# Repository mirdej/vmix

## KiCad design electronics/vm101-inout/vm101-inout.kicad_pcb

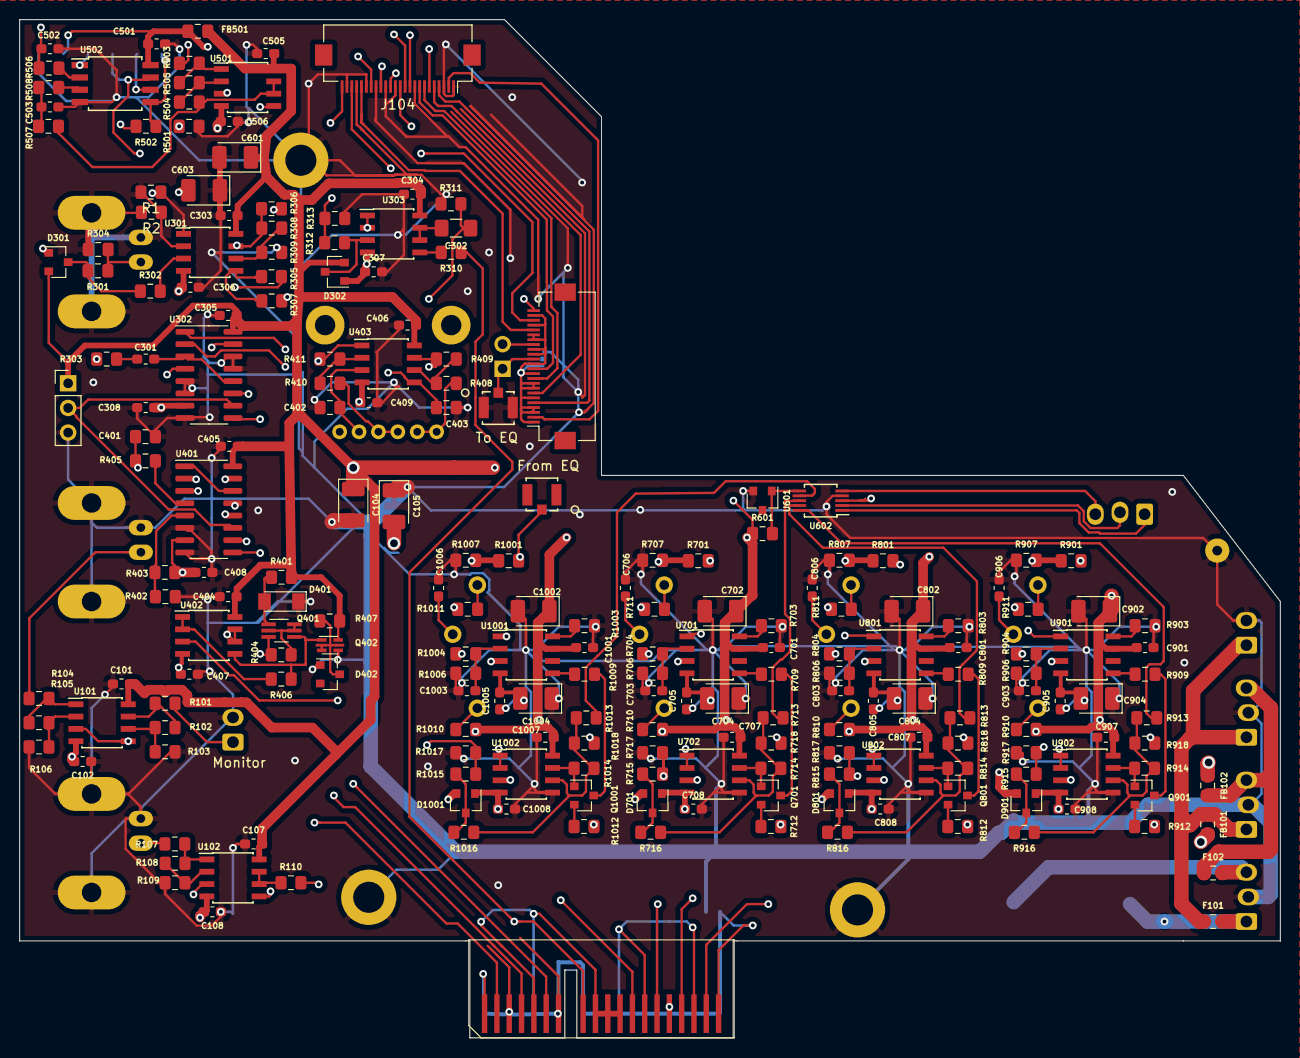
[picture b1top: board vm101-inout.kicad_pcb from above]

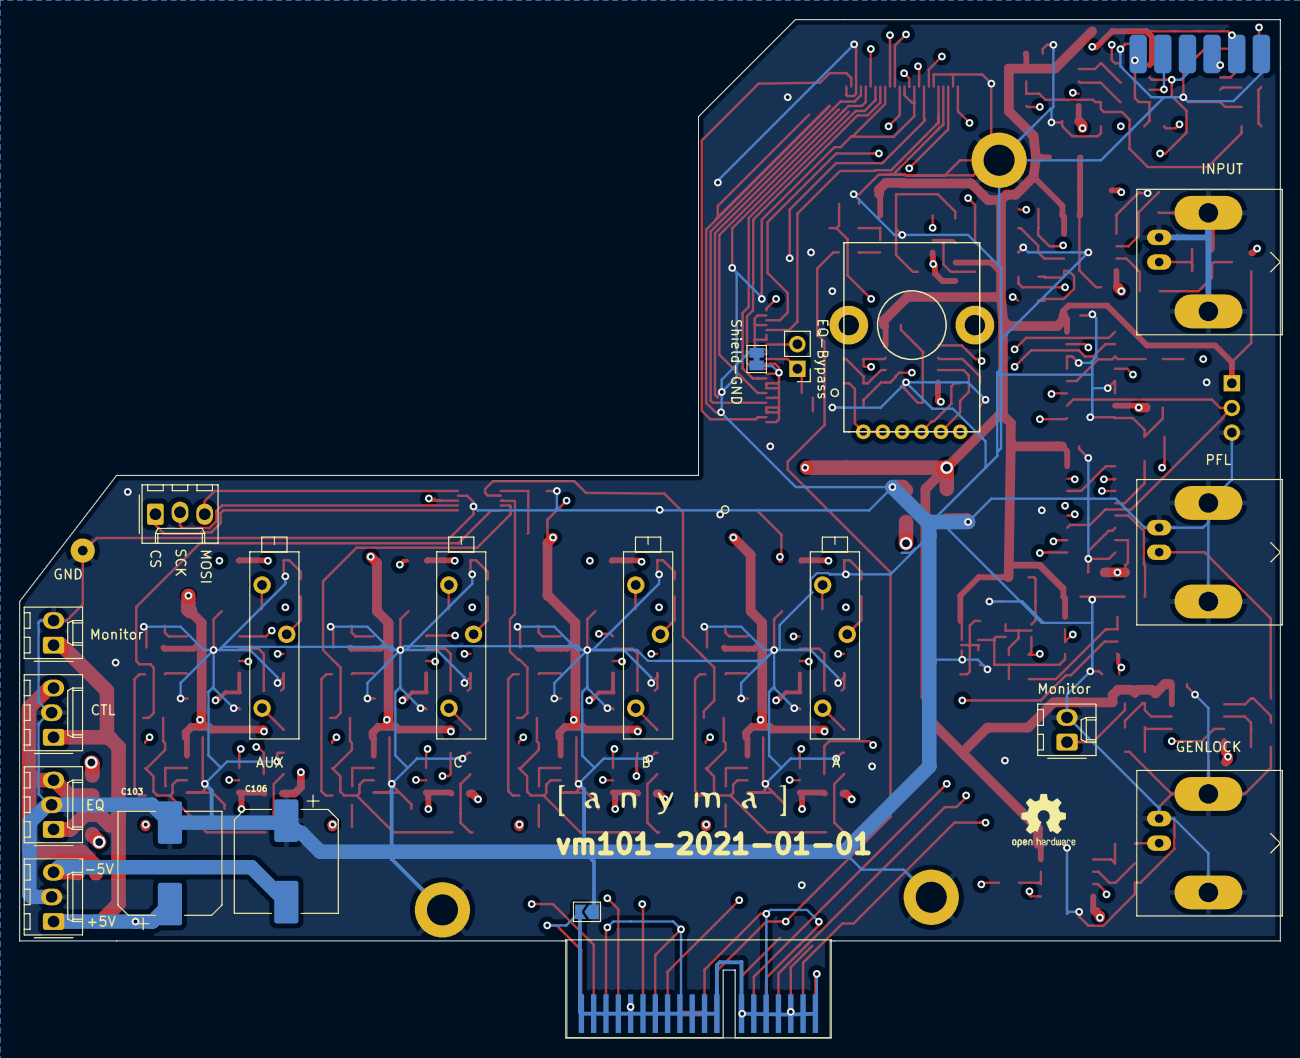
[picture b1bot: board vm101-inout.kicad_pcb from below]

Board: 4 copper layers, 130.0 x 105.0 mm, 238 parts (22 on the bottom side), 150 nets.

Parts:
C101, C102, C107, C108, C303, C304, C305, C306, C307, C308, C404, C405, C406, C407, C408, C409, C501, C505, C506, C701, C705, C707, C708, C801, C805, C807, C808, C901, C905, C907, C908, C1001, C1005, C1007, C1008: 100n; C_0603_1608Metric_Pad1.05x0.95mm_HandSolder
C103, C106: 220u; CP_Elec_10x10.5
C104, C105, C601, C603: 10u; CP_EIA-3528-21_Kemet-B_Pad1.50x2.35mm_HandSolder
C301, C703, C706, C803, C806, C903, C906, C1003, C1006: 1u; C_0603_1608Metric_Pad1.05x0.95mm_HandSolder
C302: 0-Ohm; C_1206_3216Metric_Pad1.42x1.75mm_HandSolder
C401: don't; C_0805_2012Metric_Pad1.15x1.40mm_HandSolder
C402, C403: 10p; C_0805_2012Metric_Pad1.15x1.40mm_HandSolder
C502, C503: C_Small; C_0603_1608Metric_Pad1.05x0.95mm_HandSolder
C702, C704, C802, C804, C902, C904, C1002, C1004: 4u7; CP_EIA-3528-21_Kemet-B_Pad1.50x2.35mm_HandSolder
D301, D302, D701, D801, D901, D1001: BAT54S; SOT-23
D401: D; D_MiniMELF
D402: BAT54; D_SOT-23_ANK
F101, F102: Polyfuse; Fuse_0805_2012Metric
FB101, FB102: 330u; L_0805_2012Metric_Pad1.15x1.40mm_HandSolder
FB501: Ferrit(flash levelmeter first); L_0805_2012Metric_Pad1.15x1.40mm_HandSolder
H601, H602, H603: MountingHole_Pad; MountingHole_3.2mm_M3_ISO7380_Pad
J101: Conn_Coaxial; BNC_Amphenol_B6252HB-NPP3G-50_Horizontal
J102: MONITOR_OUT; Molex_KK-254_AE-6410-02A_1x02_P2.54mm_Vertical
J103: To EQ; Hirose_FH12-24S-0.5SH_1x24-1MP_P0.50mm_Horizontal
J104: Conn_01x24_Shielded; Hirose_FH12-24S-0.5SH_1x24-1MP_P0.50mm_Horizontal
J105: PFL-OUT; BNC_Amphenol_B6252HB-NPP3G-50_Horizontal
J106: GENLOCK-OUT; BNC_Amphenol_B6252HB-NPP3G-50_Horizontal
J107: gnd; Solderpad_1mm
J108: Monitor-Power; Molex_KK-254_AE-6410-02A_1x02_P2.54mm_Vertical
J109: EQ-Power; Molex_KK-254_AE-6410-03A_1x03_P2.54mm_Vertical
J110: Controller-Power; Molex_KK-254_AE-6410-03A_1x03_P2.54mm_Vertical
J111: Card-Edge_02x20_Odd_Even; Samtec_MECF-20-0_-L-DV_2x20_P1.27mm_Polarized_Edge
J112: Power; Molex_KK-254_AE-6410-03A_1x03_P2.54mm_Vertical
J113: Conn_01x03; PinHeader_1x03_P2.54mm_Vertical
J114, J115: TE_UMCC_2337019-1
J601: Conn_01x03; Molex_KK-254_AE-6410-03A_1x03_P2.54mm_Vertical
JP101: Jumper_2_Open; PinHeader_1x02_P2.54mm_Vertical
JP102: Jumper; SolderJumper-2_P1.3mm_Bridged_Pad1.0x1.5mm
JP103: Jumper; SolderJumper-2_P1.3mm_Open_TrianglePad1.0x1.5mm
Q401: PMBT3906YS; SOT-363_SC-70-6_Handsoldering
Q402: PEMX1; SOT-666
Q701, Q801, Q901, Q1001: PNP; SOT-23_BEC
R1: 680; R_0805_2012Metric_Pad1.15x1.40mm_HandSolder
R2: 1k6; R_0805_2012Metric_Pad1.15x1.40mm_HandSolder
R101, R104, R107, R110, R301, R302, R303, R304, R306, R310, R312, R506, R508: 75; R_0805_2012Metric_Pad1.15x1.40mm_HandSolder
R102, R103, R105, R106, R108, R109, R408, R409, R410, R411: 220; R_0805_2012Metric_Pad1.15x1.40mm_HandSolder
R305, R307, R308, R309, R501, R503, R504, R505, R507: 3k3; R_0805_2012Metric_Pad1.15x1.40mm_HandSolder
R311: don't; R_0805_2012Metric_Pad1.15x1.40mm_HandSolder
R313: 10k; R_0805_2012Metric_Pad1.15x1.40mm_HandSolder
R401, R405, R703, R803, R903, R1003: 120; R_0805_2012Metric_Pad1.15x1.40mm_HandSolder
R402, R406, R502: 300; R_0805_2012Metric_Pad1.15x1.40mm_HandSolder
R403: 4k7; R_0805_2012Metric_Pad1.15x1.40mm_HandSolder
R404: 5k6; R_0805_2012Metric_Pad1.15x1.40mm_HandSolder
R407, R717, R817, R917, R1017: 47k; R_0805_2012Metric_Pad1.15x1.40mm_HandSolder
R601: 560; R_0805_2012Metric_Pad1.15x1.40mm_HandSolder
R701, R709, R801, R809, R901, R909, R1001, R1009: 1k; R_0805_2012Metric_Pad1.15x1.40mm_HandSolder
R704, R710, R711, R804, R810, R811, R904, R910, R911, R1004, R1010, R1011: 3k; R_0805_2012Metric_Pad1.15x1.40mm_HandSolder
R706, R707, R715, R806, R807, R815, R906, R907, R915, R1006, R1007, R1015: 100; R_0805_2012Metric_Pad1.15x1.40mm_HandSolder
R712, R812, R912, R1012: 2k2; R_0805_2012Metric_Pad1.15x1.40mm_HandSolder
R713, R716, R813, R816, R913, R916, R1013, R1016: 12K; R_0805_2012Metric_Pad1.15x1.40mm_HandSolder
R714, R814, R914, R1014: 20k; R_0805_2012Metric_Pad1.15x1.40mm_HandSolder
R718, R818, R918, R1018: 22k; R_0805_2012Metric_Pad1.15x1.40mm_HandSolder
RV401: R_POT_Dual; RK12L123
RV701, RV801, RV901, RV1001: 500; Potentiometer_Bourns_3006P_Horizontal
U101, U102: MAX4392; SOIC-8_3.9x4.9mm_P1.27mm
U301, U303, U402, U403, U702, U802, U902, U1002: LMH6643; SOIC-8_3.9x4.9mm_P1.27mm
U302, U401: 4053; SOIC-16_3.9x9.9mm_P1.27mm
U501: Opamp_Dual_Generic; SOIC-8_3.9x4.9mm_P1.27mm
U502: ATtiny85-20SU; SOIJ-8_5.3x5.3mm_P1.27mm
U503: AnymaISP; Pinhead_SMD_6
U601: ADR510; SOT-23
U602: MAX5741; MSOP-10_3x3mm_P0.5mm
U701, U801, U901, U1001: LT1228; SOIC-8_3.9x4.9mm_P1.27mm
U1003: LOGO; logo_anyma
U1004: LOGO; OSHW-Logo2_7.3x6mm_SilkScreen

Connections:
+5V: C101.2, C104.1, C107.2, C303.2, C304.2, C305.2, C404.2, C405.2, C406.2, C505.1, C601.1, C701.2, C702.1, C707.1, C801.2, C802.1, C807.1, C901.2, C902.1, C907.1, C1001.2, C1002.1, C1007.1, D301.2, D302.2, D701.2, D801.2, D901.2, D1001.2, FB101.2, FB501.2, J113.1, Q402.6 (C), R401.2, R407.1, R601.1, R710.2, R712.2, R810.2, R812.2, R910.2, R912.2, R1010.2, R1012.2, U101.8 (V+), U102.8 (V+), U301.8 (V+), U302.16 (VDD), U303.8 (V+), U401.16 (VDD), U402.8 (V+), U403.8 (V+), U501.8 (V+), U602.3 (VDD), U701.7 (Vcc), U702.8 (V+), U801.7 (Vcc), U802.8 (V+), U901.7 (Vcc), U902.8 (V+), U1001.7 (Vcc), U1002.8 (V+)
-5V: C102.2, C105.2, C108.2, C306.1, C307.1, C308.1, C407.1, C408.1, C409.1, C506.1, C603.2, C704.2, C705.2, C708.1, C804.2, C805.2, C808.1, C904.2, C905.2, C908.1, C1004.2, C1005.2, C1008.1, D301.1, D302.1, D701.1, D801.1, D901.1, D1001.1, FB102.2, Q401.3 (C), R403.2, R404.1, R711.1, R718.1, R811.1, R818.1, R911.1, R918.1, R1011.1, R1018.1, U101.4 (V-), U102.4 (V-), U301.4 (V-), U302.7 (VEE), U303.4 (V-), U401.7 (VEE), U402.4 (V-), U403.4 (V-), U501.4 (V-), U701.4 (Vss), U702.4 (V-), U801.4 (Vss), U802.4 (V-), U901.4 (Vss), U902.4 (V-), U1001.4 (Vss), U1002.4 (V-)
/Input-Clamp/INPUT-Composite: J101.1 (In), R301.1, R304.2
/Input-Clamp/clamped: R305.1, U302.4 (Z)
/Levelmeter/miso: U502.6 (RX|OC1A|OC0B|MISO|PB1|1), U503.5 (MISO)
/Levelmeter/mosi: R502.1, U502.5 (AREF|TX|OC0A|SDA|MOSI|PB0|0), U503.6 (MOSI)
/Levelmeter/reset: U502.1 (~RESET|A0|PB5|5), U503.3 (~RESET)
/Mixer/dac_a: R1013.2, U602.7 (OUTA)
/Mixer/dac_b: R713.2, U602.8 (OUTB)
/Mixer/dac_c: R813.2, U602.9 (OUTC)
/Mixer/dac_d: R913.2, U602.10 (OUTD)
/Mixer/dac_select: J601.1, U602.1 (~CS)
/Mixer/mosi: J601.3, U602.5 (DIN)
/Mixer/sck: J601.2, U602.2 (SCLK)
/Resyncer/OUTPUT: C401.1, R405.1, U101.3 (+), U101.5 (+)
/Resyncer/clipper_out: U401.12 (X0), U402.6 (-), U402.7
/Resyncer/synctip: R402.2, R403.1, U401.5 (Z0)
/bias: J103.22, J104.22
/compa-out: J103.2, J104.2
/from_eq: J103.17, J115.1, JP101.2 (B), R701.2, R801.2, R901.2, R1001.2, U102.5 (+), U402.3 (+), U501.5 (+)
/hi_clip1: J103.12, J104.8
/hi_clip2: J103.10, J104.7
/lo_clip1: J103.5, J104.4
/lo_clip2: J103.7, J104.5
/output-frontpanel: J104.6, R110.2
/scale: J103.20, J104.20
/siff-in: J104.24, R312.1, R313.2
/supply+: F101.1, FB101.1, J108.1, J109.1, J110.1
/supply-: F102.1, FB102.1, J109.3, J110.3
/to_eq: J103.14, J114.1, JP101.1 (A), R306.2
GND: C101.1, C102.1, C103.2, C104.2, C105.1, C106.1, C107.1, C108.1, C303.1, C304.1, C305.1, C306.2, C307.2, C308.2, C401.2, C402.2, C403.2, C404.1, C405.1, C406.1, C407.2, C408.2, C409.2, C501.2, C502.2, C503.2, C505.2, C506.2, C601.2, C603.1, C701.1, C702.2, C703.1, C704.1, C705.1, C706.1, C707.2, C708.2, C801.1, C802.2, C803.1, C804.1, C805.1, C806.1, C807.2, C808.2, C901.1, C902.2, C903.1, C904.1, C905.1, C906.1, C907.2, C908.2, C1001.1, C1002.2, C1003.1, C1004.1, C1005.1, C1006.1, C1007.2, C1008.2, D401.1 (K), D402.2 (A), H601.1, H602.1, H603.1, J101.2 (Ext), J102.2, J104.1, J104.3, J104.9, J104.13, J104.15, J104.17, J104.19, J104.21, J104.23, J105.2 (Ext), J106.2 (Ext), J107.1, J108.2, J109.2, J110.2, J112.2, J113.3, J114.2, J114.3, JP102.1, JP103.1, Q402.4 (E), R2.2, R103.1, R106.1, R109.1, R304.1, R309.2, R311.1, R313.1, R402.1, R501.2, R703.2, R706.1, R707.1, R717.1, R803.2, R806.1, R807.1, R817.1, R903.2, R906.1, R907.1, R917.1, R1003.2, R1006.1, R1007.1, R1017.1, U302.5 (Z0), U302.6 (Inh), U302.8 (VSS), U302.13 (X1), U302.14 (X), U401.6 (Inh), U401.8 (VSS), U502.4 (GND), U503.1 (GND), U601.2 (V-), U602.4 (GND), U702.5 (+), U802.5 (+), U902.5 (+), U1002.5 (+)
unnamed: C103.1, F101.2, J112.1
unnamed: C106.2, F102.2, J112.3
unnamed: C301.1, U302.3 (Z1), U302.12 (X0)
unnamed: C301.2, R303.1
unnamed: C302.2, U303.6 (-), U303.7
unnamed: C402.1, RV401.6, U403.3 (+)
unnamed: C403.1, RV401.3, U403.5 (+)
unnamed: C502.1, R503.1, R506.1
unnamed: C503.1, R507.1, R508.1
unnamed: C703.2, R704.1, R706.2, U701.2 (-In)
unnamed: C706.2, RV701.2, U702.3 (+)
unnamed: C803.2, R804.1, R806.2, U801.2 (-In)
unnamed: C806.2, RV801.2, U802.3 (+)
unnamed: C903.2, R904.1, R906.2, U901.2 (-In)
unnamed: C906.2, RV901.2, U902.3 (+)
unnamed: C1003.2, R1004.1, R1006.2, U1001.2 (-In)
unnamed: C1006.2, RV1001.2, U1002.3 (+)
unnamed: D301.3, R301.2, R302.1
unnamed: D302.3, R312.2, U303.3 (+)
unnamed: D401.2 (A), Q401.1 (E), R401.1
unnamed: D402.1 (K), Q402.2 (B), Q402.3 (C), Q402.5 (B), R407.2
unnamed: D701.3, R715.1, R716.2
unnamed: D801.3, R815.1, R816.2
unnamed: D901.3, R915.1, R916.2
unnamed: D1001.3, R1015.1, R1016.2
unnamed: J102.1, R101.2
unnamed: J103.1, J103.3, J103.4, J103.6, J103.8, J103.9, J103.11, J103.13, J103.15, J103.16, J103.18, J103.19, J103.21, J103.23, JP102.2
unnamed: J105.1 (In), R104.2
unnamed: J106.1 (In), R107.2
unnamed: J111.1, J111.2, J111.4, J111.5, J111.6, J111.8, J111.9, J111.10, J111.12, J111.13, J111.14, J111.18, J111.19, J111.20, J111.21, J111.22, J111.23, J111.24, J111.26, J111.27, J111.28, J111.30, J111.31, J111.32, J111.34, J111.35, J111.36, J111.38, J111.39, J111.40, JP103.2
unnamed: Q401.2 (B), Q401.5 (B), Q401.6 (C), R404.2
unnamed: Q401.4 (E), Q402.1 (E), R406.1, U402.5 (+)
unnamed: Q701.B, R714.1, U702.7
unnamed: Q701.C, R709.1
unnamed: Q701.E, R712.1
unnamed: Q801.B, R814.1, U802.7
unnamed: Q801.C, R809.1
unnamed: Q801.E, R812.1
unnamed: Q901.B, R914.1, U902.7
unnamed: Q901.C, R909.1
unnamed: Q901.E, R912.1
unnamed: Q1001.B, R1014.1, U1002.7
unnamed: Q1001.C, R1009.1
unnamed: Q1001.E, R1012.1
unnamed: R101.1, R102.1, U101.7
unnamed: R102.2, R103.2, U101.6 (-)
unnamed: R104.1, R105.1, U101.1
unnamed: R105.2, R106.2, U101.2 (-)
unnamed: R107.1, R108.1, U102.1
unnamed: R108.2, R109.2, U102.2 (-)
unnamed: R110.1, U102.6 (-), U102.7
unnamed: R302.2, U301.3 (+)
unnamed: R1.1, R303.2, U301.1
unnamed: R305.2, R307.2, U301.5 (+)
unnamed: R307.1, U303.1, U303.2 (-)
unnamed: R308.1, R309.1, U301.6 (-)
unnamed: R310.2, U303.5 (+)
unnamed: R405.2, U401.4 (Z)
unnamed: R406.2, U402.1, U402.2 (-)
unnamed: R408.1, R409.2, U403.6 (-)
unnamed: R409.1, R410.2, RV401.4, RV401.5, U403.7
unnamed: R410.1, R411.2, U403.2 (-)
unnamed: R501.1, U501.3 (+)
unnamed: R503.2, R505.1, U501.1
unnamed: R504.1, R505.2, U501.2 (-)
unnamed: R504.2, R507.2, U501.6 (-), U501.7
unnamed: R506.2, U502.2 (A3|XTAL1/PB3|3)
unnamed: R508.2, U502.3 (A2|OC1B|XTAL2/PB4|4)
unnamed: R601.2, U601.1 (V+), U602.6 (REF)
unnamed: R701.1, R707.2, U701.3 (+In)
unnamed: R703.1, U701.8 (Gain)
unnamed: R704.2, U702.1, U702.2 (-)
unnamed: R709.2, U701.5 (Iset)
unnamed: R710.1, RV701.1
unnamed: R711.2, RV701.3
unnamed: R713.1, R714.2, R716.1, R718.2, U702.6 (-)
unnamed: R801.1, R807.2, U801.3 (+In)
unnamed: R803.1, U801.8 (Gain)
unnamed: R804.2, U802.1, U802.2 (-)
unnamed: R809.2, U801.5 (Iset)
unnamed: R810.1, RV801.1
unnamed: R811.2, RV801.3
unnamed: R813.1, R814.2, R816.1, R818.2, U802.6 (-)
unnamed: R901.1, R907.2, U901.3 (+In)
unnamed: R903.1, U901.8 (Gain)
unnamed: R904.2, U902.1, U902.2 (-)
unnamed: R909.2, U901.5 (Iset)
unnamed: R910.1, RV901.1
unnamed: R911.2, RV901.3
unnamed: R913.1, R914.2, R916.1, R918.2, U902.6 (-)
unnamed: R1001.1, R1007.2, U1001.3 (+In)
unnamed: R1003.1, U1001.8 (Gain)
unnamed: R1004.2, U1002.1, U1002.2 (-)
unnamed: R1009.2, U1001.5 (Iset)
unnamed: R1010.1, RV1001.1
unnamed: R1011.2, RV1001.3
unnamed: R1013.1, R1014.2, R1016.1, R1018.2, U1002.6 (-)
unnamed: R1.2, R2.1, U301.2 (-)
unnamed: U401.1 (Y1), U401.14 (X)
unnamed: U401.3 (Z1), U401.15 (Y)
VCC: C501.1, FB501.1, J104.11, U502.8 (VCC), U503.2 (VCC)
colorburst: C302.1, R311.2, R408.2, RV401.1, RV401.2, U302.1 (Y1)
cv_a: J104.12, R1015.2, R1017.2
cv_b: J104.14, R715.2, R717.2
cv_c: J104.16, R815.2, R817.2
cv_d: J104.18, R915.2, R917.2
delayed_burst: R411.1, U302.2 (Y0), U403.1
dry: R306.1, R308.2, U301.7, U401.13 (X1)
dry~wet: J103.24, J113.2, U302.10 (B), U401.11 (A)
genlock: J111.17, R310.1, U102.3 (+)
hsync: J111.7, U302.9 (C), U401.9 (C)
out_a: J111.25, U1001.1 (Iout)
out_b: J111.29, U701.1 (Iout)
out_c: J111.33, U801.1 (Iout)
out_d: J111.37, U901.1 (Iout)
pixels: J104.10, R502.2
porch: J111.3, U302.11 (A), U401.10 (B)
preview_burst: U302.15 (Y), U401.2 (Y0)
vsync: J111.11, U502.7 (A1|SCK|SCL|INT0|PB2|2), U503.4 (SCK)

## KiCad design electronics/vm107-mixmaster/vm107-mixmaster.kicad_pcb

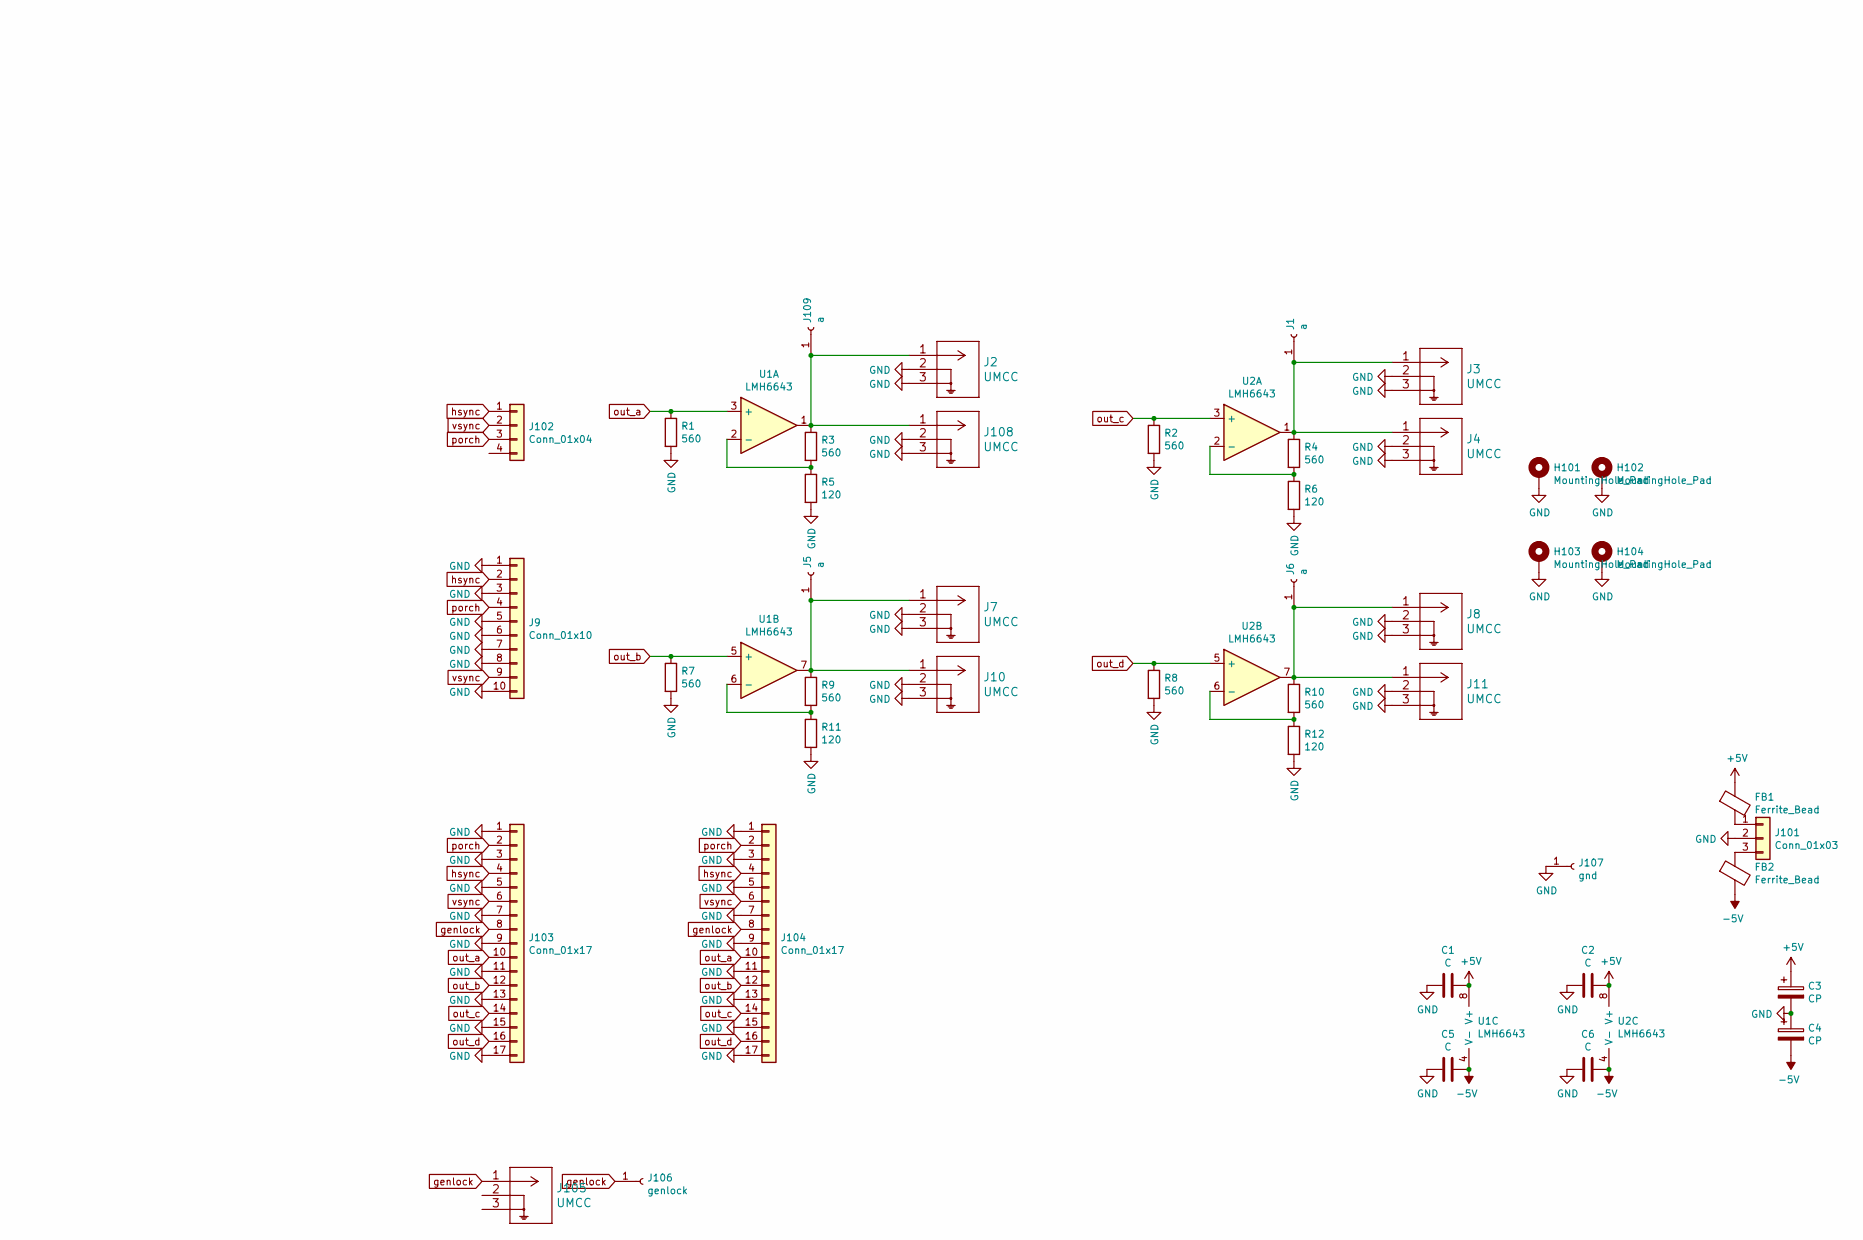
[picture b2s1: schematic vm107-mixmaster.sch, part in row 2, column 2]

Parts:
C1, C2, C5, C6: C; C_0603_1608Metric_Pad1.05x0.95mm_HandSolder
C3, C4: CP; CP_EIA-3528-21_Kemet-B_Pad1.50x2.35mm_HandSolder
FB1, FB2: Ferrite_Bead; L_0805_2012Metric_Pad1.15x1.40mm_HandSolder
H101, H102, H103, H104: MountingHole_Pad; MountingHole_3.2mm_M3_ISO7380_Pad
J1, J5, J6, J109: a; Solderpad_1mm
J2, J3, J4, J7, J8, J10, J11, J105, J108: UMCC; TE_UMCC_2337019-1
J9: Conn_01x10; IDC-Header_2x05_P2.54mm_Vertical
J101: Conn_01x03; Molex_KK-254_AE-6410-03A_1x03_P2.54mm_Vertical
J102: Conn_01x04; Molex_KK-254_AE-6410-04A_1x04_P2.54mm_Vertical
J103, J104: Conn_01x17; 17pin-smd
J106: genlock; Solderpad_1mm
J107: gnd; Solderpad_1mm
R1, R2, R3, R4, R7, R8, R9, R10: 560; R_0805_2012Metric_Pad1.15x1.40mm_HandSolder
R5, R6, R11, R12: 120; R_0805_2012Metric_Pad1.15x1.40mm_HandSolder
U1, U2: LMH6643; SOIC-8_3.9x4.9mm_P1.27mm

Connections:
+5V: C1.1, C2.1, C3.1, FB1.1, U1.8 (V+), U2.8 (V+)
-5V: C4.2, C5.1, C6.1, FB2.2, U1.4 (V-), U2.4 (V-)
GND: C1.2, C2.2, C3.2, C4.1, C5.2, C6.2, H101.1, H102.1, H103.1, H104.1, J2.2, J2.3, J3.2, J3.3, J4.2, J4.3, J7.2, J7.3, J8.2, J8.3, J9.1, J9.3, J9.5, J9.6, J9.7, J9.8, J9.10, J10.2, J10.3, J11.2, J11.3, J101.2, J103.1, J103.3, J103.5, J103.7, J103.9, J103.11, J103.13, J103.15, J103.17, J104.1, J104.3, J104.5, J104.7, J104.9, J104.11, J104.13, J104.15, J104.17, J107.1, J108.2, J108.3, R1.2, R2.2, R5.2, R6.2, R7.2, R8.2, R11.2, R12.2
unnamed: FB1.2, J101.1
unnamed: FB2.1, J101.3
unnamed: J1.1, J3.1, J4.1, R4.1, U2.1
unnamed: J5.1, J7.1, J10.1, R9.1, U1.7
unnamed: J6.1, J8.1, J11.1, R10.1, U2.7
unnamed: J2.1, J108.1, J109.1, R3.1, U1.1
unnamed: R3.2, R5.1, U1.2 (-)
unnamed: R4.2, R6.1, U2.2 (-)
unnamed: R10.2, R12.1, U2.6 (-)
unnamed: R9.2, R11.1, U1.6 (-)
genlock: J103.8, J104.8, J105.1, J106.1
hsync: J9.2, J102.1, J103.4, J104.4
out_a: J103.10, J104.10, R1.1, U1.3 (+)
out_b: J103.12, J104.12, R7.1, U1.5 (+)
out_c: J103.14, J104.14, R2.1, U2.3 (+)
out_d: J103.16, J104.16, R8.1, U2.5 (+)
porch: J9.4, J102.3, J103.2, J104.2
vsync: J9.9, J102.2, J103.6, J104.6

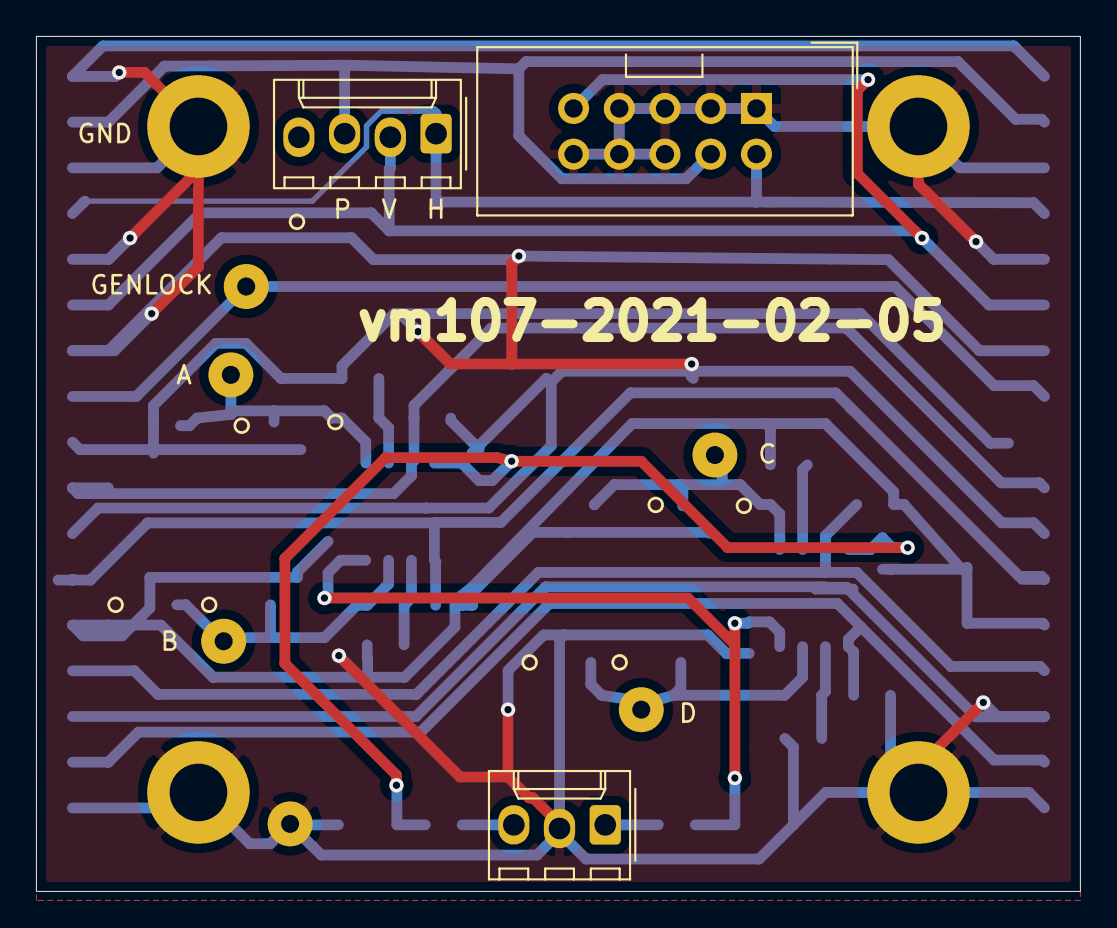
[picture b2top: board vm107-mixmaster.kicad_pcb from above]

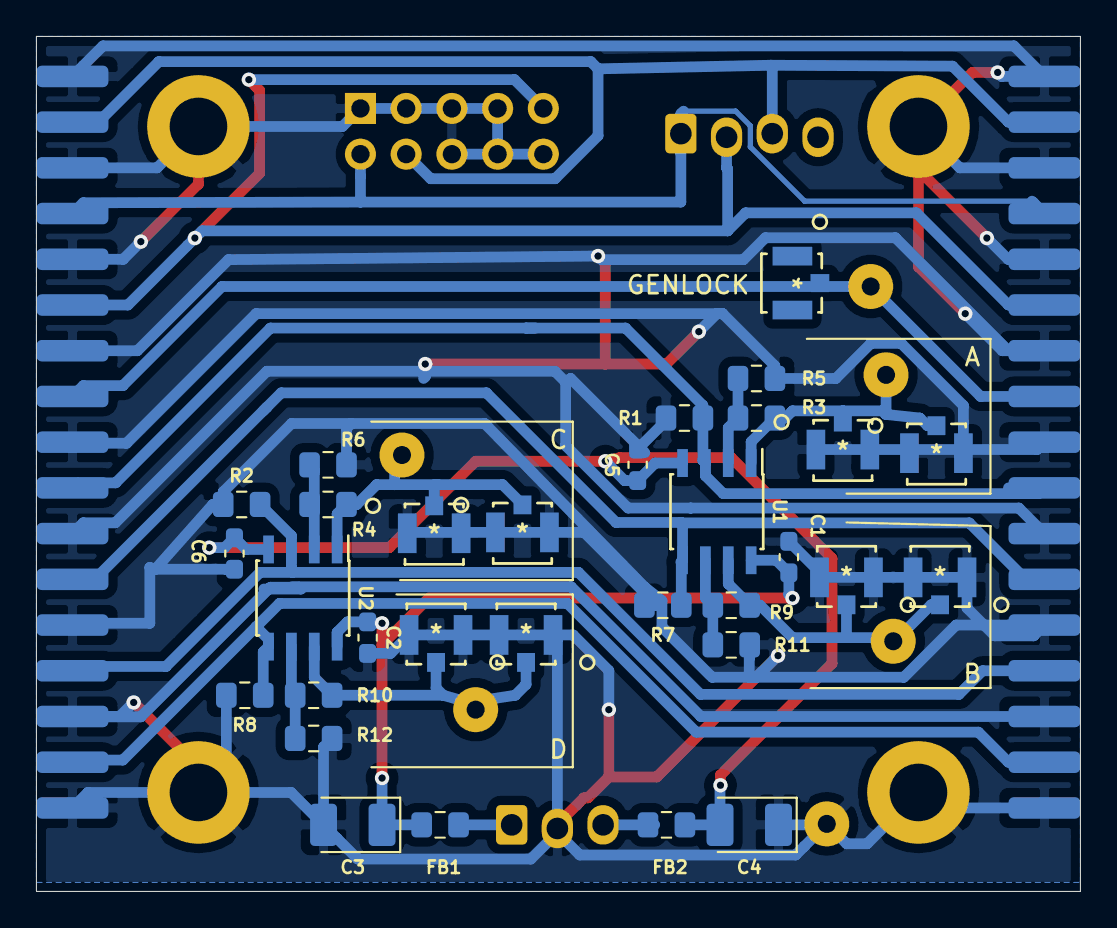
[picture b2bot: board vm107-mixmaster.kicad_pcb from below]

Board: 2 copper layers, 58.0 x 47.5 mm, 46 parts (36 on the bottom side), 21 nets.

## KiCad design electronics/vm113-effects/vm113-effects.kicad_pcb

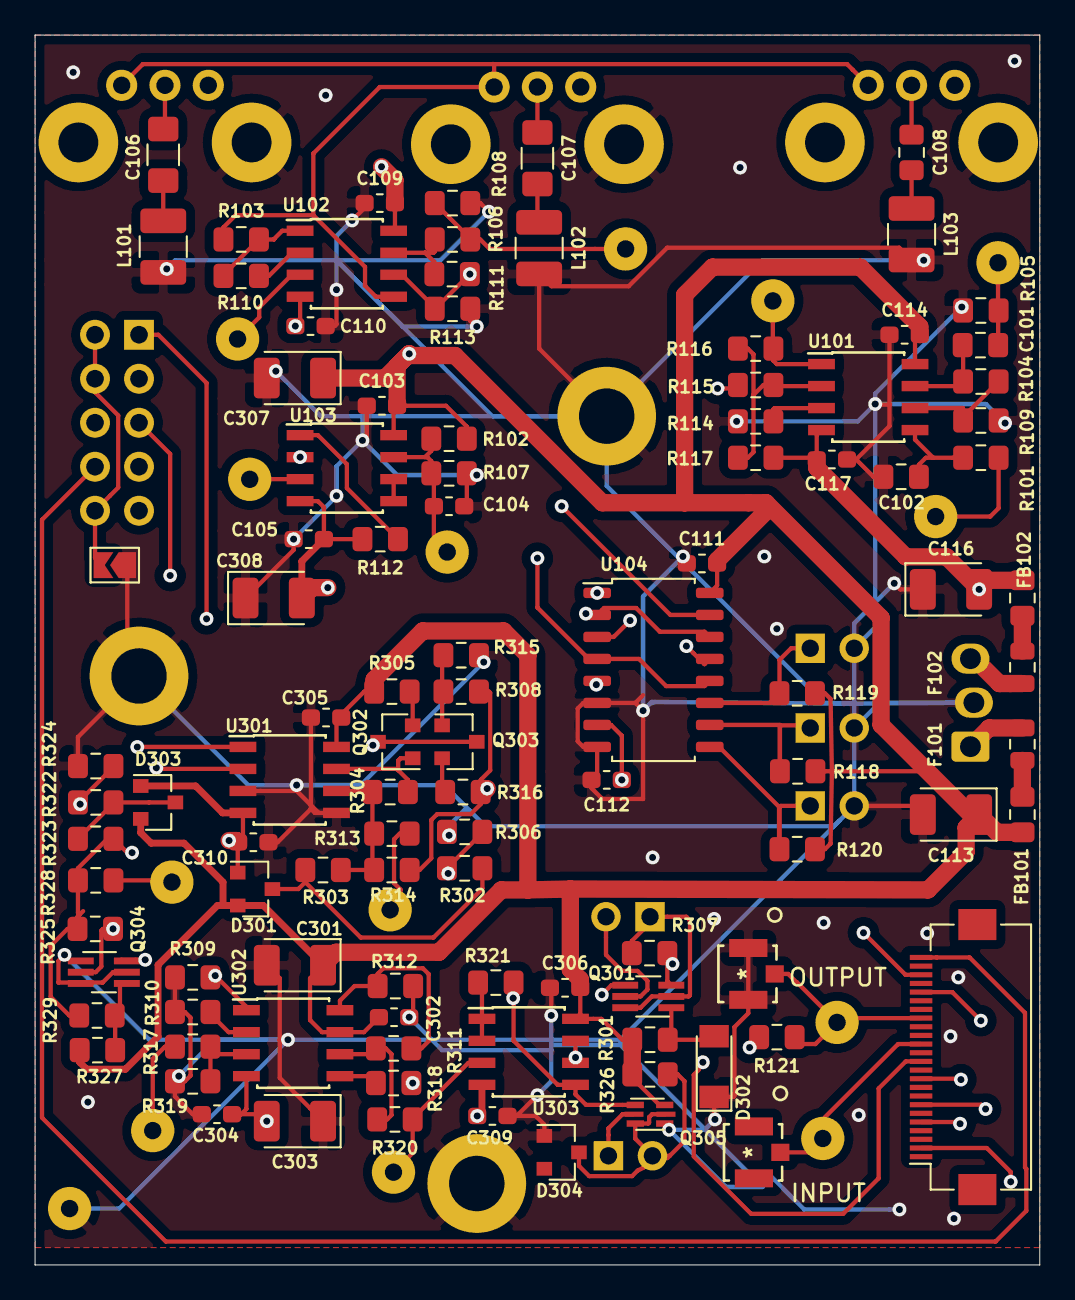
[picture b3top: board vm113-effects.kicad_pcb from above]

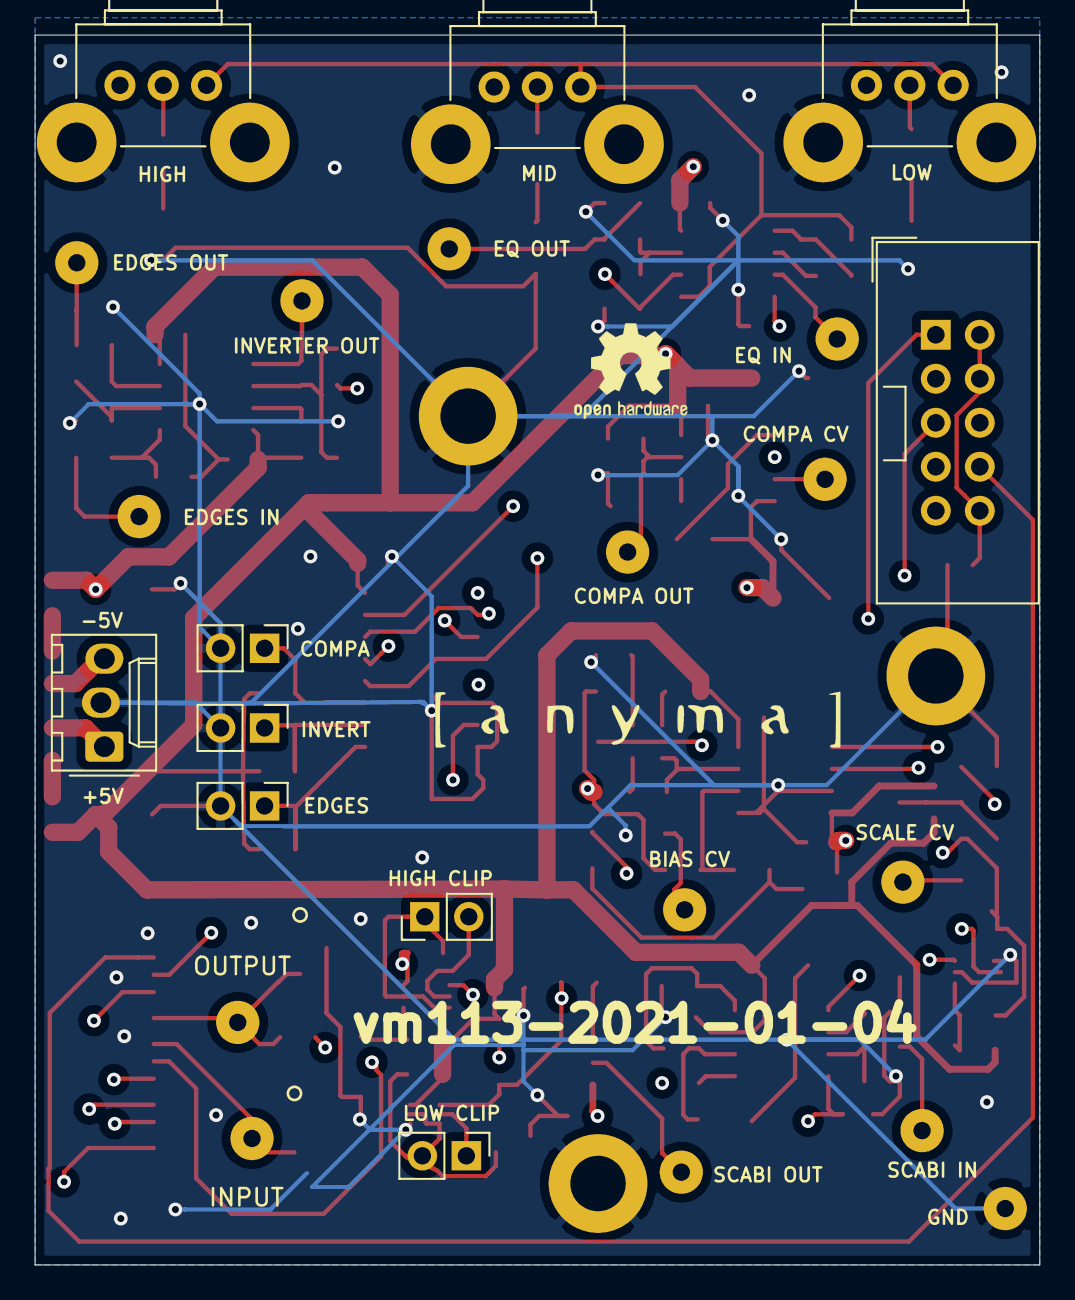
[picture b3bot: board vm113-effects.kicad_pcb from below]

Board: 4 copper layers, 58.0 x 71.0 mm, 132 parts (12 on the bottom side), 70 nets.

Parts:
C101: 1n; C_0805_2012Metric_Pad1.15x1.40mm_HandSolder
C102: 100p; C_0805_2012Metric_Pad1.15x1.40mm_HandSolder
C103, C105, C109, C110, C111, C112, C114, C117, C302, C304, C305, C306, C309, C310: 100n; C_0603_1608Metric_Pad1.05x0.95mm_HandSolder
C104: 100p-470p?; C_0603_1608Metric_Pad1.05x0.95mm_HandSolder
C106: 2u; C_1206_3216Metric_Pad1.42x1.75mm_HandSolder
C107: 300n; C_1206_3216Metric_Pad1.42x1.75mm_HandSolder
C108: 210p; C_0805_2012Metric_Pad1.15x1.40mm_HandSolder
C113, C116, C307, C308: 10u; CP_EIA-3528-21_Kemet-B_Pad1.50x2.35mm_HandSolder
C301, C303: 4u7; CP_EIA-3528-21_Kemet-B_Pad1.50x2.35mm_HandSolder
D301, D303: BAT54S; SOT-23
D302: D; D_MiniMELF
D304: BAT54; D_SOT-23_ANK
F101, F102: Polyfuse; Fuse_0805_2012Metric
FB101, FB102: 330u; L_0805_2012Metric_Pad1.15x1.40mm_HandSolder
H201, H202, H203: MountingHole_Pad; MountingHole_3.2mm_M3_ISO7380_Pad
J101: To 101; Hirose_FH12-24S-0.5SH_1x24-1MP_P0.50mm_Horizontal
J102: INPUT; Solderpad_1mm
J103: EDGES_IN; Solderpad_1mm
J104: OUTPUT; Solderpad_1mm
J105: EQ_IN; Solderpad_1mm
J106: EQ_OUT; Solderpad_1mm
J107: EDGES_OUT; Solderpad_1mm
J108: COMPA-DROP; Solderpad_1mm
J109: INVERTER-DROP; Solderpad_1mm
J110: FROM CTL; IDC-Header_2x05_P2.54mm_Vertical
J111: Power; Molex_KK-254_AE-6410-03A_1x03_P2.54mm_Vertical
J112: gnd; Solderpad_1mm
J113, J114, J115: Jumper; PinHeader_1x02_P2.54mm_Vertical
J116, J117, J118: TP; Solderpad_1mm
J119, J120: UMCC; TE_UMCC_2337019-1
J301, J304: Conn_01x02; PinHeader_1x02_P2.54mm_Vertical
J302: SCABI_OUT; Solderpad_1mm
J303: SCABI_IN; Solderpad_1mm
JP102: Jumper; SolderJumper-2_P1.3mm_Open_TrianglePad1.0x1.5mm
L101: 330u; L_1210_3225Metric_Pad1.42x2.65mm_HandSolder
L102: 330uH; L_1210_3225Metric_Pad1.42x2.65mm_HandSolder
L103: 1.19uH; L_1210_3225Metric_Pad1.42x2.65mm_HandSolder
Q301, Q304: PMBT3906YS; SOT-363_SC-70-6_Handsoldering
Q302: PNP; SOT-23_BEC
Q303: BC847; SOT-23_BEC
Q305: PEMX1; SOT-666
R101, R311, R318, R319: 1k; R_0805_2012Metric_Pad1.15x1.40mm_HandSolder
R102, R309, R321: 300; R_0805_2012Metric_Pad1.15x1.40mm_HandSolder
R103, R111, R113, R114, R115, R116: 2k2; R_0805_2012Metric_Pad1.15x1.40mm_HandSolder
R104: 30k; R_0805_2012Metric_Pad1.15x1.40mm_HandSolder
R105, R312: 100; R_0805_2012Metric_Pad1.15x1.40mm_HandSolder
R106, R107, R108, R110, R121, R302, R320, R322: 75; R_0805_2012Metric_Pad1.15x1.40mm_HandSolder
R109, R118, R119, R120, R314: 15k; R_0805_2012Metric_Pad1.15x1.40mm_HandSolder
R112: 220; R_0805_2012Metric_Pad1.15x1.40mm_HandSolder
R117: 16k; R_0805_2012Metric_Pad1.15x1.40mm_HandSolder
R301: 120; R_0805_2012Metric_Pad1.15x1.40mm_HandSolder
R303, R304, R306, R308, R315, R317, R324, R327: 10k; R_0805_2012Metric_Pad1.15x1.40mm_HandSolder
R305, R316: 3k3; R_0805_2012Metric_Pad1.15x1.40mm_HandSolder
R307: 5k6; R_0805_2012Metric_Pad1.15x1.40mm_HandSolder
R310: 560; R_0805_2012Metric_Pad1.15x1.40mm_HandSolder
R313: 5.1k; R_0805_2012Metric_Pad1.15x1.40mm_HandSolder
R323, R328: 100k; R_0805_2012Metric_Pad1.15x1.40mm_HandSolder
R325, R329: 4k7; R_0805_2012Metric_Pad1.15x1.40mm_HandSolder
R326: 47k; R_0805_2012Metric_Pad1.15x1.40mm_HandSolder
RV101: LOW; Potentiometer_Alps_RK09K_Single_Horizontal
RV102: MID; Potentiometer_Alps_RK09K_Single_Horizontal
RV103: HIGH; Potentiometer_Alps_RK09K_Single_Horizontal
U101, U102, U301, U303: LMH6643; SOIC-8_3.9x4.9mm_P1.27mm
U103: LM311; SOIC-8_3.9x4.9mm_P1.27mm
U104: MAX4053; SOP-16_4.55x10.3mm_P1.27mm
U201: LOGO; logo_anyma
U202: LOGO; OSHW-Logo2_7.3x6mm_SilkScreen
U302: LT1228; SOIC-8_3.9x4.9mm_P1.27mm

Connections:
+5V: C103.2, C109.2, C111.2, C113.1, C114.2, C301.1, C302.2, C305.2, C306.2, C307.1, D301.2, D303.2, FB101.2, Q305.6, R102.1, R118.1, R119.1, R120.1, R301.1, R305.1, R326.1, R327.1, U101.8, U102.8, U103.8, U104.16, U301.8, U302.7, U303.8
-5V: C105.1, C110.1, C112.1, C116.2, C117.1, C303.2, C304.2, C308.2, C309.1, C310.2, D301.1, D303.1, FB102.2, Q301.3, R112.2, R117.2, R307.2, R314.2, R315.2, R316.2, U101.4, U102.4, U103.4, U104.7, U301.4, U302.4, U303.4
/Scabi/Clip/OUTPUT: R121.2, U303.6, U303.7
/Scabi/Clip/scabi-out: J302.1, R320.1, U303.3
/compa_in: U103.2, U104.4, U104.12
/compa_out: C104.2, J101.2, J108.1, R102.2, R107.1, U103.7, U104.13
/edges_in: J101.14, J102.1, J103.1, J119.1, R101.2, U104.5
/edges_out: C101.2, J107.1, R105.2, U104.3
/eq_in: J105.1, U102.3, U104.15
/eq_out: J106.1, J303.1, R106.1, R108.2, R317.1
/inverter_in: R115.2, U104.2, U104.14
/inverter_out: J109.1, R116.1, U101.1, U104.1
/to-101: J101.17, J104.1, J120.1, R121.1
BIAS-IN: J101.22, R302.1, R306.2
GND: C102.1, C103.1, C104.1, C105.2, C109.1, C110.2, C111.1, C112.2, C113.2, C114.1, C116.1, C117.2, C301.2, C302.1, C303.1, C304.1, C305.1, C306.1, C307.2, C308.1, C309.2, C310.1, D302.1, D304.2, H201.1, H202.1, H203.1, J111.2, J112.1, J113.2, J114.2, J115.2, J120.2, J120.3, JP102.1, L101.2, L102.2, L103.2, Q304.1, Q304.3, Q304.5, Q305.4, R105.1, R107.2, R108.1, R109.2, R113.1, R114.1, R306.1, R308.1, R309.1, R310.1, R312.1, R319.1, R324.1, U104.6, U104.8, U301.3, U301.5
unnamed: C101.1, R104.1, U101.7
unnamed: C102.2, R101.1, U101.5
unnamed: C106.1, RV101.2
unnamed: C106.2, L101.1
unnamed: C107.1, RV102.2
unnamed: C107.2, L102.1
unnamed: C108.1, RV103.2
unnamed: C108.2, L103.1
unnamed: D301.3, R302.2, R303.1
unnamed: D302.2, Q301.1, R301.2
unnamed: D303.3, R322.2, R323.1
unnamed: F101.1, FB101.1
unnamed: F101.2, J111.1
unnamed: F102.1, FB102.1
unnamed: F102.2, J111.3
unnamed: J110.2, J110.4, J110.10, JP102.2
unnamed: Q301.4, Q305.1, R321.1, U303.5
unnamed: Q302.B, R304.2, U301.7
unnamed: Q302.C, Q303.C, R309.2, U302.1
unnamed: Q302.E, R305.2
unnamed: Q303.B, R308.2, R315.1
unnamed: Q303.E, R316.1
unnamed: Q304.2, R325.2, U301.1
unnamed: Q304.4, R327.2, R329.2
unnamed: Q304.6, R318.2
unnamed: R103.1, RV101.1, RV102.1, RV103.1, U102.5
unnamed: R103.2, R110.1, U102.1
unnamed: R104.2, R109.1, U101.6
unnamed: R106.2, R111.1, U102.7
unnamed: R110.2, U102.2
unnamed: R111.2, R113.2, RV101.3, RV102.3, RV103.3, U102.6
unnamed: R112.1, U103.1
unnamed: R114.2, U101.3
unnamed: R115.1, R116.2, R117.1, U101.2
unnamed: R303.2, R304.1, R313.2, R314.1, U301.6
unnamed: R310.2, U302.2
unnamed: R311.1, R320.2, U302.6
unnamed: R311.2, R312.2, U302.8
unnamed: R317.2, R319.2, U302.3
unnamed: R318.1, U302.5
unnamed: R321.2, U303.1, U303.2
unnamed: R323.2, R325.1, R328.2, R329.1, U301.2
unnamed: U103.5, U103.6
SCALE-IN: J101.20, R322.1, R324.2
bias_cv: J110.9, J117.1, R313.1
compa_bypass: J110.6, J114.1, R119.2, U104.11
compa_cv: J110.3, J118.1, U103.3
dry~wet~: J101.24, J110.8
edges_bypass: J110.5, J115.1, R120.2, U104.9
hi_clip_1: J101.12, J301.1, Q301.2, Q301.6, R307.1
hi_clip_2: J101.10, J301.2, Q301.5
inverter_bypass: J110.7, J113.1, R118.2, U104.10
lo_clip_1: J101.5, J304.1, Q305.2
lo_clip_2: D304.1, J101.7, J304.2, Q305.3, Q305.5, R326.2
scale_cv: J110.1, J116.1, R328.1

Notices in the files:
parts and their libraries:
Copyright 2016 Accelerated Designs. All rights reserved.
